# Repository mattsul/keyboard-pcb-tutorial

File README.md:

# Introduction
This repository will cover the ai03 keyboard tutorial using KiCad.

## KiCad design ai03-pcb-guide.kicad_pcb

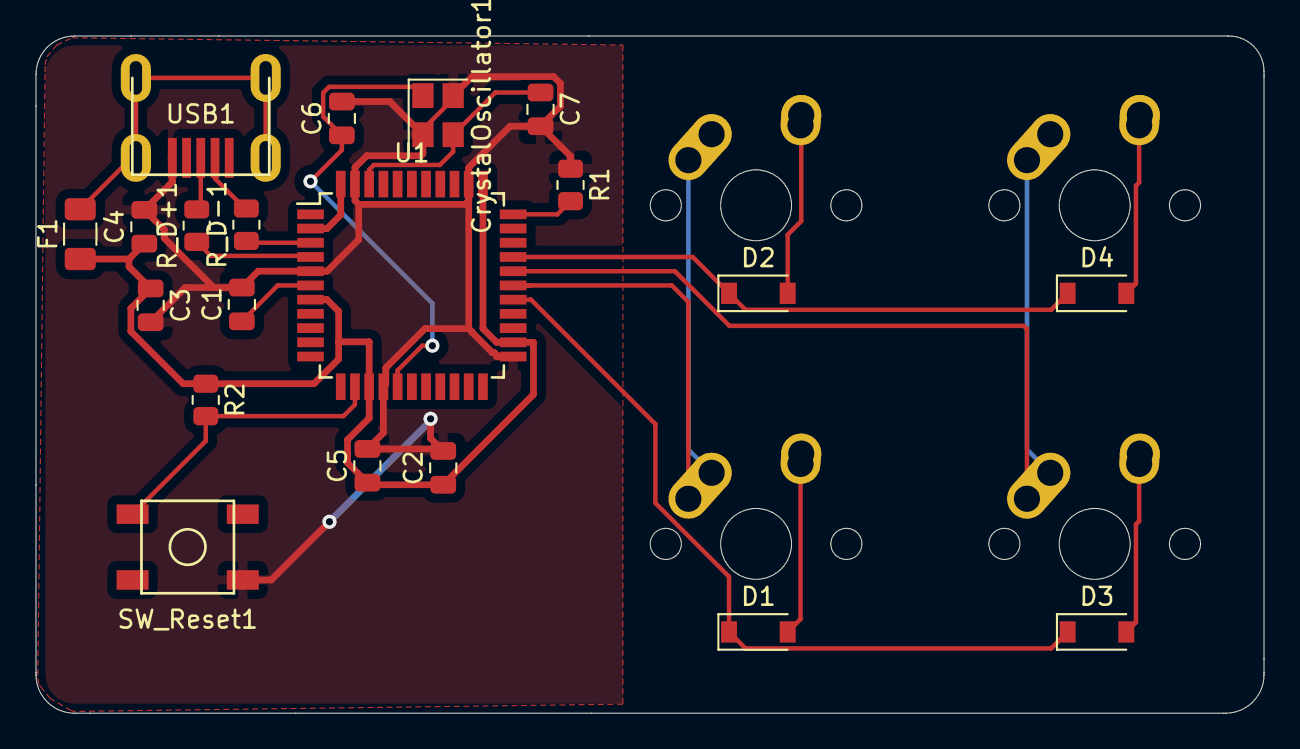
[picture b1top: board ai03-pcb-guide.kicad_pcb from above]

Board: 2 copper layers, 69.1 x 38.1 mm, 24 parts (0 on the bottom side), 20 nets.

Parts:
C1: 1uF; C_0805_2012Metric
C2, C3: 0.1uF; C_0805_2012Metric
C4: 0.01uF; C_0805_2012Metric
C5: 10uF; C_0805_2012Metric
C6, C7: 22pF; C_0805_2012Metric
CrystalOscillator1: 16 MHz; Crystal_SMD_3225-4Pin_3.2x2.5mm
D1, D2, D3, D4: D_Small; D_SOD-123
F1: 500mA; Fuse_1206_3216Metric
MX1, MX2, MX3, MX4: MX-NoLED; MX-1U-NoLED
R1: 10k; R_0805_2012Metric
R2: R_Small; R_0805_2012Metric
R_D+1: 22; R_0805_2012Metric
R_D-1: 22; R_0805_2012Metric
SW_Reset1: SW_Push; SKQG-1155865
U1: ATmega32U4-AU; TQFP-44_10x10mm_P0.8mm
USB1: Molex-0548190589

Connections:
+5V: C2.1, C3.1, C4.1, C5.1, F1.1, R2.1, U1.2, U1.7, U1.14, U1.24, U1.34, U1.44
COL0: MX1.1, MX2.1, U1.28
COL1: MX3.1, MX4.1, U1.29
D+: R_D+1.2, USB1.3
D-: R_D-1.2, USB1.4
GND: C1.2, C2.2, C3.2, C4.2, C5.2, C6.2, C7.2, CrystalOscillator1.2, CrystalOscillator1.4, R1.1, SW_Reset1.1, U1.5, U1.15, U1.23, U1.35, U1.43, USB1.1
unnamed: C1.1, U1.6
unnamed: C6.1, CrystalOscillator1.1, U1.16
unnamed: C7.1, CrystalOscillator1.3, U1.42
unnamed: D1.2, MX1.2
unnamed: D2.2, MX2.2
unnamed: D3.2, MX3.2
unnamed: D4.2, MX4.2
unnamed: R1.2, U1.33
unnamed: R2.2, SW_Reset1.2, U1.13
unnamed: R_D+1.1, U1.4
unnamed: R_D-1.1, U1.3
ROW0: D1.1, D3.1, U1.27
ROW1: D2.1, D4.1, U1.30
VCC: F1.2, USB1.6

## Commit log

2021-10-14 Initialized KiCad Project
    Added empty KiCad files.
    .sch = schematic
    .kicad_pcb = pcb file
2021-10-14 Added dependencies: footprints for cherry MX switches and USB connectors
2021-10-14 Added schematic and footprint libraries to project
2021-10-14 Schematic and PCB layout completed
2021-10-15 Final Touches
    Ready to be printed and made.
